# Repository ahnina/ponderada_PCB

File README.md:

A seguinte atividade foi realizada no software Kicad. Na pasta "pasta_com_arquivos_kicad" encontram todos os arquivos referentes ao projeto a serem executados pelo Kicad.
Entre eles, incluem se: "ponderada_PCB.kicad.pro" que executa o projeto inteiro no software, "ponderada_PCB.kicad_sch" que é o arquivo que contem o esquemático e "ponderada_PCB.kicad_pcb" 
que é o arquivo que contém a montagem gráfica da placa.

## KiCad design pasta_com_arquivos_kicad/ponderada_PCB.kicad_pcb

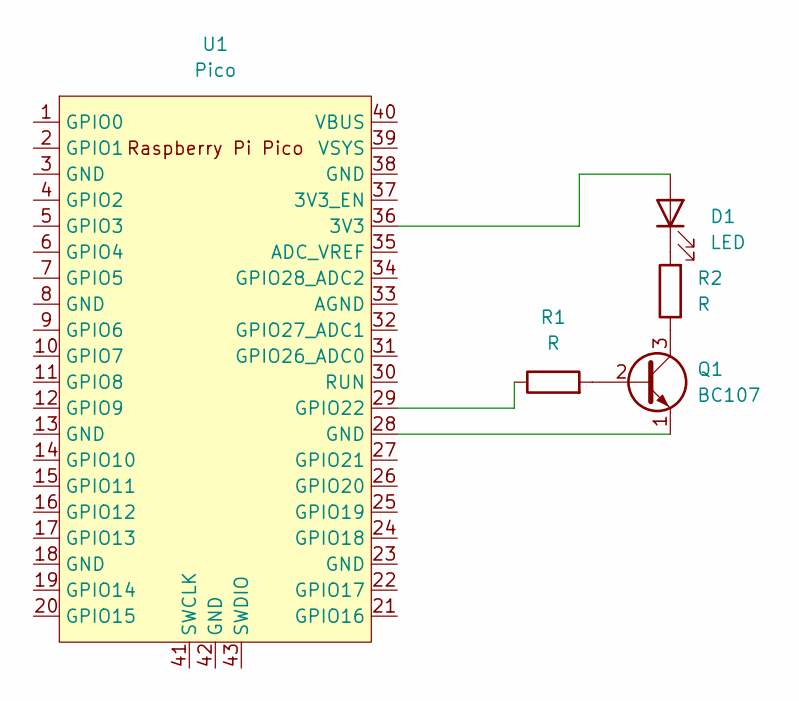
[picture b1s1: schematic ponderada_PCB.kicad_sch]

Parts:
D1: LED; LED_D10.0mm
Q1: BC107; TO-18-3
R1, R2: R; R_0201_0603Metric
U1: Pico; RPi_Pico_SMD_TH

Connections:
unnamed: D1.2 (A), U1.36 (3V3)
unnamed: D1.1 (K), R2.2
unnamed: Q1.2 (B), R1.2
unnamed: Q1.3 (C), R2.1
unnamed: Q1.1 (E), U1.28 (GND)
unnamed: R1.1, U1.29 (GPIO22)

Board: 2 copper layers, 5 parts (0 on the bottom side), 6 nets, no tracks yet.

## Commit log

2024-04-01 criando repositorio
